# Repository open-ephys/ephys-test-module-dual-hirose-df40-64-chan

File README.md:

# Test Module for two Hirose DF40-based Headstages

This test module works with the Open Ephys
[automated ephys tester](https://github.com/open-ephys/ephys-test-board). 
It can be used to verify the functionality of:

- [Low profile 64-channel Standard](https://github.com/open-ephys/low-profile-spi-headstage-64ch)
- [Low profile 64 channel 3D](https://github.com/open-ephys/low-profile-3d-headstage-64ch)
- [ONIX Headstage-64](https://github.com/open-ephys/onix-headstage-64)
- [ONIX Headstage-64e](https://github.com/open-ephys/onix-headstage-64s)
- [ONIX Headstage-16 Stim](https://github.com/open-ephys/onix-headstage-16stim)

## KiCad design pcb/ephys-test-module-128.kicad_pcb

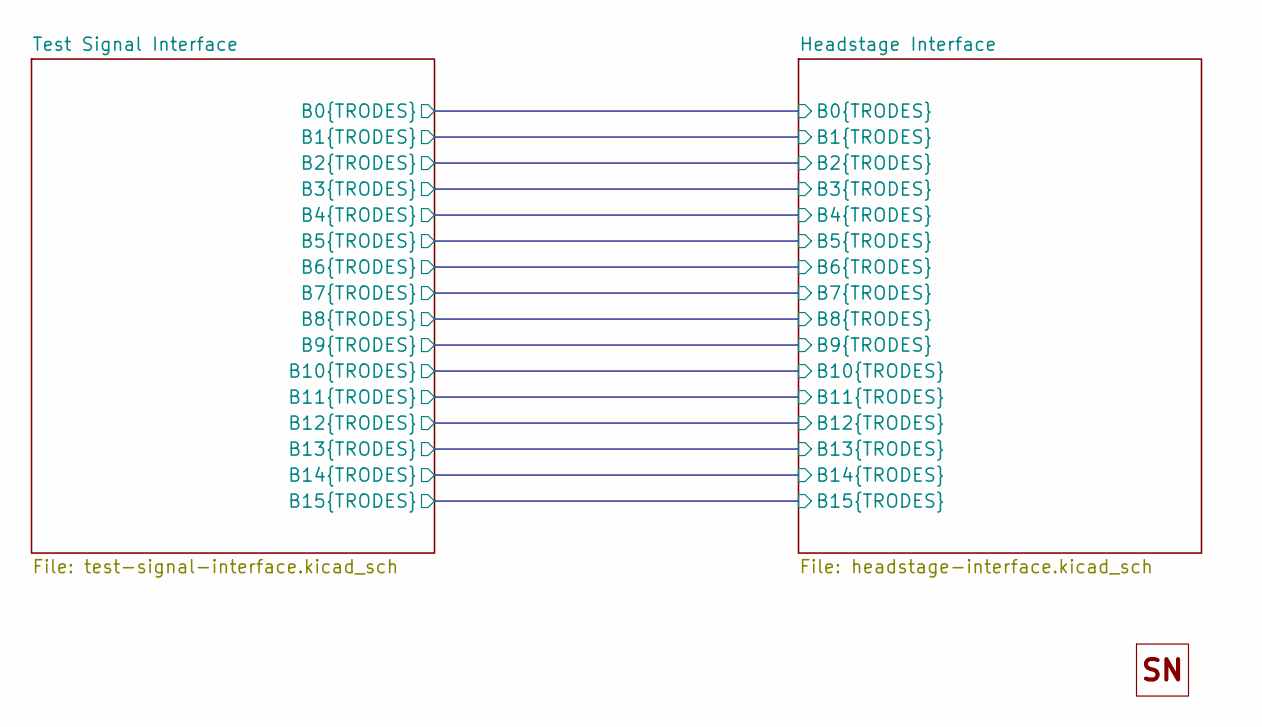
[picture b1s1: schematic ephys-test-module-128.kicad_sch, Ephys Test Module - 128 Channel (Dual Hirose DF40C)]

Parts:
H1: SN; OEPS_SN-STICKER-8x20mm; MPN n.a.

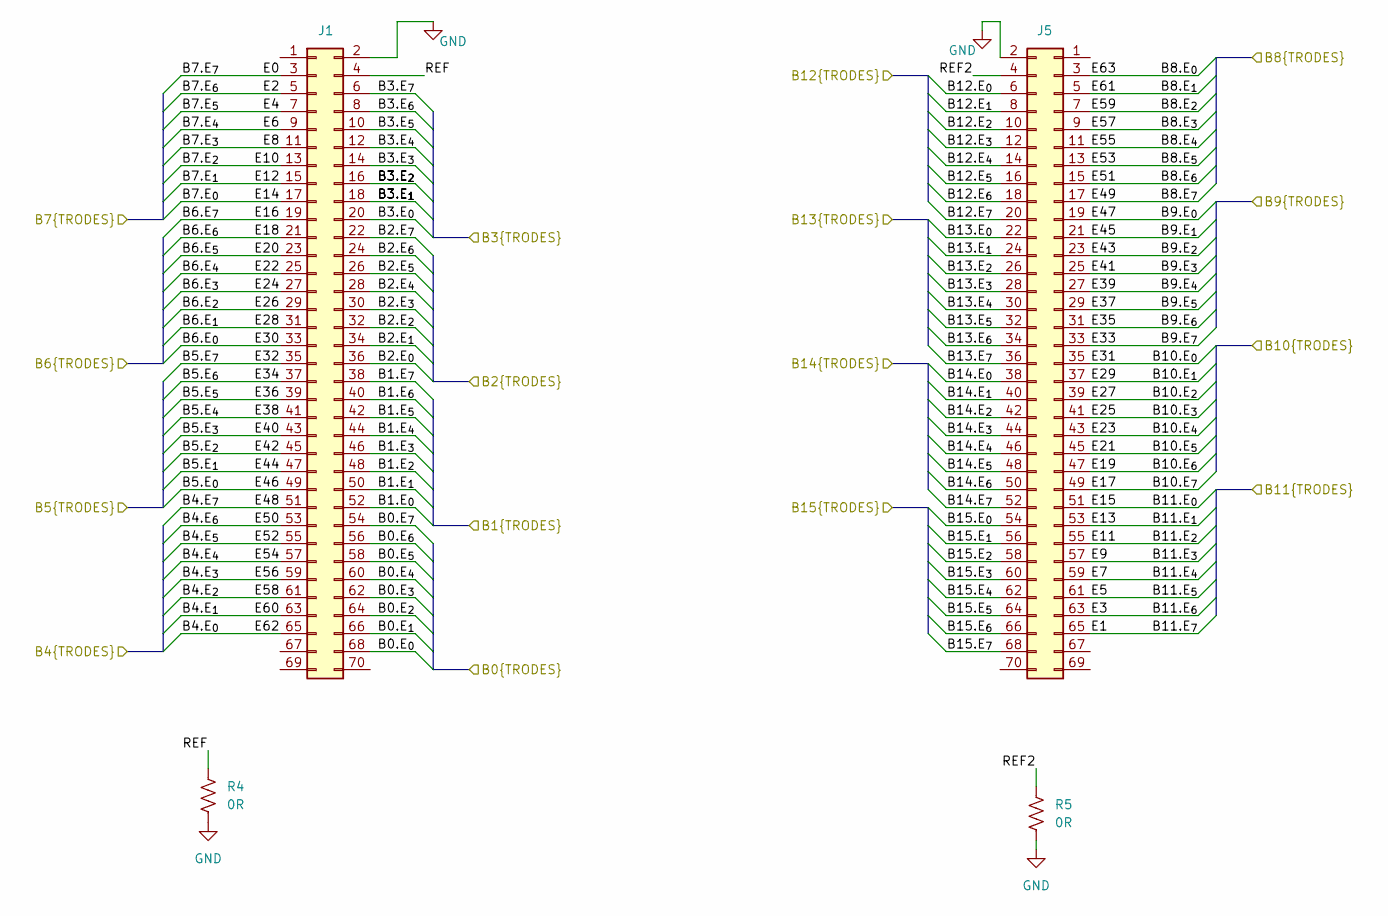
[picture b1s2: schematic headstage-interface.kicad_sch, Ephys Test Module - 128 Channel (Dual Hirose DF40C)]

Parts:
J1, J5: DF40C(2.0)-70DS-0.4V(51); HIROSE_DF40C(2.0)-70DS-0.4V(51); MPN DF40C(2.0)-70DS-0.4V(51)
R4, R5: 0R; R_0603_1608Metric; MPN RCS06030000Z0EA

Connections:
/Headstage Interface/B0.E_{0}: J1.68; also elsewhere on the board
/Headstage Interface/B0.E_{1}: J1.66; also elsewhere on the board
/Headstage Interface/B0.E_{2}: J1.64; also elsewhere on the board
/Headstage Interface/B0.E_{3}: J1.62; also elsewhere on the board
/Headstage Interface/B0.E_{4}: J1.60; also elsewhere on the board
/Headstage Interface/B0.E_{5}: J1.58; also elsewhere on the board
/Headstage Interface/B0.E_{6}: J1.56; also elsewhere on the board
/Headstage Interface/B0.E_{7}: J1.54; also elsewhere on the board
/Headstage Interface/B1.E_{0}: J1.52; also elsewhere on the board
/Headstage Interface/B1.E_{1}: J1.50; also elsewhere on the board
/Headstage Interface/B1.E_{2}: J1.48; also elsewhere on the board
/Headstage Interface/B1.E_{3}: J1.46; also elsewhere on the board
/Headstage Interface/B1.E_{4}: J1.44; also elsewhere on the board
/Headstage Interface/B1.E_{5}: J1.42; also elsewhere on the board
/Headstage Interface/B1.E_{6}: J1.40; also elsewhere on the board
/Headstage Interface/B1.E_{7}: J1.38; also elsewhere on the board
/Headstage Interface/B2.E_{0}: J1.36; also elsewhere on the board
/Headstage Interface/B2.E_{1}: J1.34; also elsewhere on the board
/Headstage Interface/B2.E_{2}: J1.32; also elsewhere on the board
/Headstage Interface/B2.E_{3}: J1.30; also elsewhere on the board
/Headstage Interface/B2.E_{4}: J1.28; also elsewhere on the board
/Headstage Interface/B2.E_{5}: J1.26; also elsewhere on the board
/Headstage Interface/B2.E_{6}: J1.24; also elsewhere on the board
/Headstage Interface/B2.E_{7}: J1.22; also elsewhere on the board
/Headstage Interface/B3.E_{0}: J1.20; also elsewhere on the board
/Headstage Interface/B3.E_{1}: J1.18; also elsewhere on the board
/Headstage Interface/B3.E_{2}: J1.16; also elsewhere on the board
/Headstage Interface/B3.E_{3}: J1.14; also elsewhere on the board
/Headstage Interface/B3.E_{4}: J1.12; also elsewhere on the board
/Headstage Interface/B3.E_{5}: J1.10; also elsewhere on the board
/Headstage Interface/B3.E_{6}: J1.8; also elsewhere on the board
/Headstage Interface/B3.E_{7}: J1.6; also elsewhere on the board
/Headstage Interface/B4.E_{0}: J1.65; also elsewhere on the board
/Headstage Interface/B4.E_{1}: J1.63; also elsewhere on the board
/Headstage Interface/B4.E_{2}: J1.61; also elsewhere on the board
/Headstage Interface/B4.E_{3}: J1.59; also elsewhere on the board
/Headstage Interface/B4.E_{4}: J1.57; also elsewhere on the board
/Headstage Interface/B4.E_{5}: J1.55; also elsewhere on the board
/Headstage Interface/B4.E_{6}: J1.53; also elsewhere on the board
/Headstage Interface/B4.E_{7}: J1.51; also elsewhere on the board
/Headstage Interface/B5.E_{0}: J1.49; also elsewhere on the board
/Headstage Interface/B5.E_{1}: J1.47; also elsewhere on the board
/Headstage Interface/B5.E_{2}: J1.45; also elsewhere on the board
/Headstage Interface/B5.E_{3}: J1.43; also elsewhere on the board
/Headstage Interface/B5.E_{4}: J1.41; also elsewhere on the board
/Headstage Interface/B5.E_{5}: J1.39; also elsewhere on the board
/Headstage Interface/B5.E_{6}: J1.37; also elsewhere on the board
/Headstage Interface/B5.E_{7}: J1.35; also elsewhere on the board
/Headstage Interface/B6.E_{0}: J1.33; also elsewhere on the board
/Headstage Interface/B6.E_{1}: J1.31; also elsewhere on the board
/Headstage Interface/B6.E_{2}: J1.29; also elsewhere on the board
/Headstage Interface/B6.E_{3}: J1.27; also elsewhere on the board
/Headstage Interface/B6.E_{4}: J1.25; also elsewhere on the board
/Headstage Interface/B6.E_{5}: J1.23; also elsewhere on the board
/Headstage Interface/B6.E_{6}: J1.21; also elsewhere on the board
/Headstage Interface/B6.E_{7}: J1.19; also elsewhere on the board
/Headstage Interface/B7.E_{0}: J1.17; also elsewhere on the board
/Headstage Interface/B7.E_{1}: J1.15; also elsewhere on the board
/Headstage Interface/B7.E_{2}: J1.13; also elsewhere on the board
/Headstage Interface/B7.E_{3}: J1.11; also elsewhere on the board
/Headstage Interface/B7.E_{4}: J1.9; also elsewhere on the board
/Headstage Interface/B7.E_{5}: J1.7; also elsewhere on the board
/Headstage Interface/B7.E_{6}: J1.5; also elsewhere on the board
/Headstage Interface/B7.E_{7}: J1.3; also elsewhere on the board
/Headstage Interface/B8.E_{0}: J5.3; also elsewhere on the board
/Headstage Interface/B8.E_{1}: J5.5; also elsewhere on the board
/Headstage Interface/B8.E_{2}: J5.7; also elsewhere on the board
/Headstage Interface/B8.E_{3}: J5.9; also elsewhere on the board
/Headstage Interface/B8.E_{4}: J5.11; also elsewhere on the board
/Headstage Interface/B8.E_{5}: J5.13; also elsewhere on the board
/Headstage Interface/B8.E_{6}: J5.15; also elsewhere on the board
/Headstage Interface/B8.E_{7}: J5.17; also elsewhere on the board
/Headstage Interface/B9.E_{0}: J5.19; also elsewhere on the board
/Headstage Interface/B9.E_{1}: J5.21; also elsewhere on the board
/Headstage Interface/B9.E_{2}: J5.23; also elsewhere on the board
/Headstage Interface/B9.E_{3}: J5.25; also elsewhere on the board
/Headstage Interface/B9.E_{4}: J5.27; also elsewhere on the board
/Headstage Interface/B9.E_{5}: J5.29; also elsewhere on the board
/Headstage Interface/B9.E_{6}: J5.31; also elsewhere on the board
/Headstage Interface/B9.E_{7}: J5.33; also elsewhere on the board
/Headstage Interface/B10.E_{0}: J5.35; also elsewhere on the board
/Headstage Interface/B10.E_{1}: J5.37; also elsewhere on the board
/Headstage Interface/B10.E_{2}: J5.39; also elsewhere on the board
/Headstage Interface/B10.E_{3}: J5.41; also elsewhere on the board
/Headstage Interface/B10.E_{4}: J5.43; also elsewhere on the board
/Headstage Interface/B10.E_{5}: J5.45; also elsewhere on the board
/Headstage Interface/B10.E_{6}: J5.47; also elsewhere on the board
/Headstage Interface/B10.E_{7}: J5.49; also elsewhere on the board
/Headstage Interface/B11.E_{0}: J5.51; also elsewhere on the board
/Headstage Interface/B11.E_{1}: J5.53; also elsewhere on the board
/Headstage Interface/B11.E_{2}: J5.55; also elsewhere on the board
/Headstage Interface/B11.E_{3}: J5.57; also elsewhere on the board
/Headstage Interface/B11.E_{4}: J5.59; also elsewhere on the board
/Headstage Interface/B11.E_{5}: J5.61; also elsewhere on the board
/Headstage Interface/B11.E_{6}: J5.63; also elsewhere on the board
/Headstage Interface/B11.E_{7}: J5.65; also elsewhere on the board
/Headstage Interface/B12.E_{0}: J5.6; also elsewhere on the board
/Headstage Interface/B12.E_{1}: J5.8; also elsewhere on the board
/Headstage Interface/B12.E_{2}: J5.10; also elsewhere on the board
/Headstage Interface/B12.E_{3}: J5.12; also elsewhere on the board
/Headstage Interface/B12.E_{4}: J5.14; also elsewhere on the board
/Headstage Interface/B12.E_{5}: J5.16; also elsewhere on the board
/Headstage Interface/B12.E_{6}: J5.18; also elsewhere on the board
/Headstage Interface/B12.E_{7}: J5.20; also elsewhere on the board
/Headstage Interface/B13.E_{0}: J5.22; also elsewhere on the board
/Headstage Interface/B13.E_{1}: J5.24; also elsewhere on the board
/Headstage Interface/B13.E_{2}: J5.26; also elsewhere on the board
/Headstage Interface/B13.E_{3}: J5.28; also elsewhere on the board
/Headstage Interface/B13.E_{4}: J5.30; also elsewhere on the board
/Headstage Interface/B13.E_{5}: J5.32; also elsewhere on the board
/Headstage Interface/B13.E_{6}: J5.34; also elsewhere on the board
/Headstage Interface/B13.E_{7}: J5.36; also elsewhere on the board
/Headstage Interface/B14.E_{0}: J5.38; also elsewhere on the board
/Headstage Interface/B14.E_{1}: J5.40; also elsewhere on the board
/Headstage Interface/B14.E_{2}: J5.42; also elsewhere on the board
/Headstage Interface/B14.E_{3}: J5.44; also elsewhere on the board
/Headstage Interface/B14.E_{4}: J5.46; also elsewhere on the board
/Headstage Interface/B14.E_{5}: J5.48; also elsewhere on the board
/Headstage Interface/B14.E_{6}: J5.50; also elsewhere on the board
/Headstage Interface/B14.E_{7}: J5.52; also elsewhere on the board
/Headstage Interface/B15.E_{0}: J5.54; also elsewhere on the board
/Headstage Interface/B15.E_{1}: J5.56; also elsewhere on the board
/Headstage Interface/B15.E_{2}: J5.58; also elsewhere on the board
/Headstage Interface/B15.E_{3}: J5.60; also elsewhere on the board
/Headstage Interface/B15.E_{4}: J5.62; also elsewhere on the board
/Headstage Interface/B15.E_{5}: J5.64; also elsewhere on the board
/Headstage Interface/B15.E_{6}: J5.66; also elsewhere on the board
/Headstage Interface/B15.E_{7}: J5.68; also elsewhere on the board
/Headstage Interface/REF: J1.4, R4.1
/Headstage Interface/REF2: J5.4, R5.1
GND: J1.2, J5.2, R4.2, R5.2; also elsewhere on the board

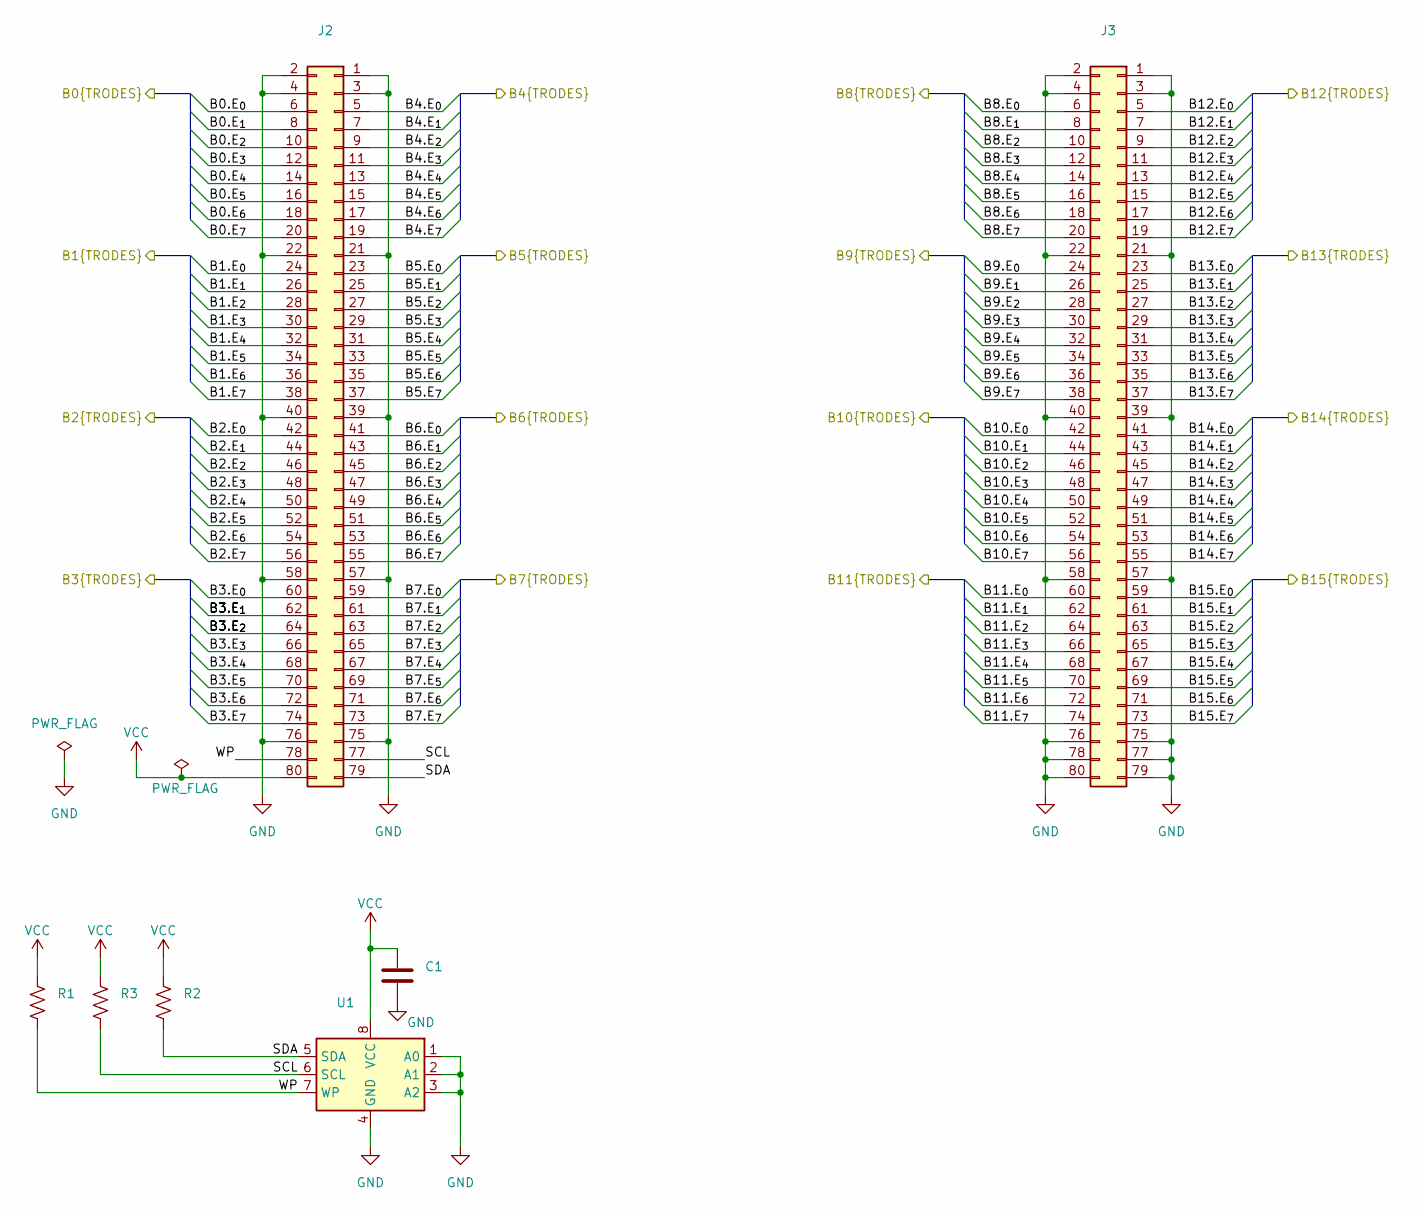
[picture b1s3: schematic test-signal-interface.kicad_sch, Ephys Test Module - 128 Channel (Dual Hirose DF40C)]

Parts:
C1: 100n; C_0402_1005Metric; MPN C1005X7R1E104K050BB
J2, J3: BSE-040-01-F-D-A-TR; SAMTEC_BSE-040-01-X-D-A; MPN BSE-040-01-F-D-A-TR
R1, R2, R3: 1k; R_0402_1005Metric; MPN CRCW04021K00FKED
U1: AT24C64D-SSHM-T; SOIC-8_3.9x4.9mm_P1.27mm; MPN AT24C64D-SSHM-T

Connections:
/Headstage Interface/B0.E_{0}: J2.6; also elsewhere on the board
/Headstage Interface/B0.E_{1}: J2.8; also elsewhere on the board
/Headstage Interface/B0.E_{2}: J2.10; also elsewhere on the board
/Headstage Interface/B0.E_{3}: J2.12; also elsewhere on the board
/Headstage Interface/B0.E_{4}: J2.14; also elsewhere on the board
/Headstage Interface/B0.E_{5}: J2.16; also elsewhere on the board
/Headstage Interface/B0.E_{6}: J2.18; also elsewhere on the board
/Headstage Interface/B0.E_{7}: J2.20; also elsewhere on the board
/Headstage Interface/B1.E_{0}: J2.24; also elsewhere on the board
/Headstage Interface/B1.E_{1}: J2.26; also elsewhere on the board
/Headstage Interface/B1.E_{2}: J2.28; also elsewhere on the board
/Headstage Interface/B1.E_{3}: J2.30; also elsewhere on the board
/Headstage Interface/B1.E_{4}: J2.32; also elsewhere on the board
/Headstage Interface/B1.E_{5}: J2.34; also elsewhere on the board
/Headstage Interface/B1.E_{6}: J2.36; also elsewhere on the board
/Headstage Interface/B1.E_{7}: J2.38; also elsewhere on the board
/Headstage Interface/B2.E_{0}: J2.42; also elsewhere on the board
/Headstage Interface/B2.E_{1}: J2.44; also elsewhere on the board
/Headstage Interface/B2.E_{2}: J2.46; also elsewhere on the board
/Headstage Interface/B2.E_{3}: J2.48; also elsewhere on the board
/Headstage Interface/B2.E_{4}: J2.50; also elsewhere on the board
/Headstage Interface/B2.E_{5}: J2.52; also elsewhere on the board
/Headstage Interface/B2.E_{6}: J2.54; also elsewhere on the board
/Headstage Interface/B2.E_{7}: J2.56; also elsewhere on the board
/Headstage Interface/B3.E_{0}: J2.60; also elsewhere on the board
/Headstage Interface/B3.E_{1}: J2.62; also elsewhere on the board
/Headstage Interface/B3.E_{2}: J2.64; also elsewhere on the board
/Headstage Interface/B3.E_{3}: J2.66; also elsewhere on the board
/Headstage Interface/B3.E_{4}: J2.68; also elsewhere on the board
/Headstage Interface/B3.E_{5}: J2.70; also elsewhere on the board
/Headstage Interface/B3.E_{6}: J2.72; also elsewhere on the board
/Headstage Interface/B3.E_{7}: J2.74; also elsewhere on the board
/Headstage Interface/B4.E_{0}: J2.5; also elsewhere on the board
/Headstage Interface/B4.E_{1}: J2.7; also elsewhere on the board
/Headstage Interface/B4.E_{2}: J2.9; also elsewhere on the board
/Headstage Interface/B4.E_{3}: J2.11; also elsewhere on the board
/Headstage Interface/B4.E_{4}: J2.13; also elsewhere on the board
/Headstage Interface/B4.E_{5}: J2.15; also elsewhere on the board
/Headstage Interface/B4.E_{6}: J2.17; also elsewhere on the board
/Headstage Interface/B4.E_{7}: J2.19; also elsewhere on the board
/Headstage Interface/B5.E_{0}: J2.23; also elsewhere on the board
/Headstage Interface/B5.E_{1}: J2.25; also elsewhere on the board
/Headstage Interface/B5.E_{2}: J2.27; also elsewhere on the board
/Headstage Interface/B5.E_{3}: J2.29; also elsewhere on the board
/Headstage Interface/B5.E_{4}: J2.31; also elsewhere on the board
/Headstage Interface/B5.E_{5}: J2.33; also elsewhere on the board
/Headstage Interface/B5.E_{6}: J2.35; also elsewhere on the board
/Headstage Interface/B5.E_{7}: J2.37; also elsewhere on the board
/Headstage Interface/B6.E_{0}: J2.41; also elsewhere on the board
/Headstage Interface/B6.E_{1}: J2.43; also elsewhere on the board
/Headstage Interface/B6.E_{2}: J2.45; also elsewhere on the board
/Headstage Interface/B6.E_{3}: J2.47; also elsewhere on the board
/Headstage Interface/B6.E_{4}: J2.49; also elsewhere on the board
/Headstage Interface/B6.E_{5}: J2.51; also elsewhere on the board
/Headstage Interface/B6.E_{6}: J2.53; also elsewhere on the board
/Headstage Interface/B6.E_{7}: J2.55; also elsewhere on the board
/Headstage Interface/B7.E_{0}: J2.59; also elsewhere on the board
/Headstage Interface/B7.E_{1}: J2.61; also elsewhere on the board
/Headstage Interface/B7.E_{2}: J2.63; also elsewhere on the board
/Headstage Interface/B7.E_{3}: J2.65; also elsewhere on the board
/Headstage Interface/B7.E_{4}: J2.67; also elsewhere on the board
/Headstage Interface/B7.E_{5}: J2.69; also elsewhere on the board
/Headstage Interface/B7.E_{6}: J2.71; also elsewhere on the board
/Headstage Interface/B7.E_{7}: J2.73; also elsewhere on the board
/Headstage Interface/B8.E_{0}: J3.6; also elsewhere on the board
/Headstage Interface/B8.E_{1}: J3.8; also elsewhere on the board
/Headstage Interface/B8.E_{2}: J3.10; also elsewhere on the board
/Headstage Interface/B8.E_{3}: J3.12; also elsewhere on the board
/Headstage Interface/B8.E_{4}: J3.14; also elsewhere on the board
/Headstage Interface/B8.E_{5}: J3.16; also elsewhere on the board
/Headstage Interface/B8.E_{6}: J3.18; also elsewhere on the board
/Headstage Interface/B8.E_{7}: J3.20; also elsewhere on the board
/Headstage Interface/B9.E_{0}: J3.24; also elsewhere on the board
/Headstage Interface/B9.E_{1}: J3.26; also elsewhere on the board
/Headstage Interface/B9.E_{2}: J3.28; also elsewhere on the board
/Headstage Interface/B9.E_{3}: J3.30; also elsewhere on the board
/Headstage Interface/B9.E_{4}: J3.32; also elsewhere on the board
/Headstage Interface/B9.E_{5}: J3.34; also elsewhere on the board
/Headstage Interface/B9.E_{6}: J3.36; also elsewhere on the board
/Headstage Interface/B9.E_{7}: J3.38; also elsewhere on the board
/Headstage Interface/B10.E_{0}: J3.42; also elsewhere on the board
/Headstage Interface/B10.E_{1}: J3.44; also elsewhere on the board
/Headstage Interface/B10.E_{2}: J3.46; also elsewhere on the board
/Headstage Interface/B10.E_{3}: J3.48; also elsewhere on the board
/Headstage Interface/B10.E_{4}: J3.50; also elsewhere on the board
/Headstage Interface/B10.E_{5}: J3.52; also elsewhere on the board
/Headstage Interface/B10.E_{6}: J3.54; also elsewhere on the board
/Headstage Interface/B10.E_{7}: J3.56; also elsewhere on the board
/Headstage Interface/B11.E_{0}: J3.60; also elsewhere on the board
/Headstage Interface/B11.E_{1}: J3.62; also elsewhere on the board
/Headstage Interface/B11.E_{2}: J3.64; also elsewhere on the board
/Headstage Interface/B11.E_{3}: J3.66; also elsewhere on the board
/Headstage Interface/B11.E_{4}: J3.68; also elsewhere on the board
/Headstage Interface/B11.E_{5}: J3.70; also elsewhere on the board
/Headstage Interface/B11.E_{6}: J3.72; also elsewhere on the board
/Headstage Interface/B11.E_{7}: J3.74; also elsewhere on the board
/Headstage Interface/B12.E_{0}: J3.5; also elsewhere on the board
/Headstage Interface/B12.E_{1}: J3.7; also elsewhere on the board
/Headstage Interface/B12.E_{2}: J3.9; also elsewhere on the board
/Headstage Interface/B12.E_{3}: J3.11; also elsewhere on the board
/Headstage Interface/B12.E_{4}: J3.13; also elsewhere on the board
/Headstage Interface/B12.E_{5}: J3.15; also elsewhere on the board
/Headstage Interface/B12.E_{6}: J3.17; also elsewhere on the board
/Headstage Interface/B12.E_{7}: J3.19; also elsewhere on the board
/Headstage Interface/B13.E_{0}: J3.23; also elsewhere on the board
/Headstage Interface/B13.E_{1}: J3.25; also elsewhere on the board
/Headstage Interface/B13.E_{2}: J3.27; also elsewhere on the board
/Headstage Interface/B13.E_{3}: J3.29; also elsewhere on the board
/Headstage Interface/B13.E_{4}: J3.31; also elsewhere on the board
/Headstage Interface/B13.E_{5}: J3.33; also elsewhere on the board
/Headstage Interface/B13.E_{6}: J3.35; also elsewhere on the board
/Headstage Interface/B13.E_{7}: J3.37; also elsewhere on the board
/Headstage Interface/B14.E_{0}: J3.41; also elsewhere on the board
/Headstage Interface/B14.E_{1}: J3.43; also elsewhere on the board
/Headstage Interface/B14.E_{2}: J3.45; also elsewhere on the board
/Headstage Interface/B14.E_{3}: J3.47; also elsewhere on the board
/Headstage Interface/B14.E_{4}: J3.49; also elsewhere on the board
/Headstage Interface/B14.E_{5}: J3.51; also elsewhere on the board
/Headstage Interface/B14.E_{6}: J3.53; also elsewhere on the board
/Headstage Interface/B14.E_{7}: J3.55; also elsewhere on the board
/Headstage Interface/B15.E_{0}: J3.59; also elsewhere on the board
/Headstage Interface/B15.E_{1}: J3.61; also elsewhere on the board
/Headstage Interface/B15.E_{2}: J3.63; also elsewhere on the board
/Headstage Interface/B15.E_{3}: J3.65; also elsewhere on the board
/Headstage Interface/B15.E_{4}: J3.67; also elsewhere on the board
/Headstage Interface/B15.E_{5}: J3.69; also elsewhere on the board
/Headstage Interface/B15.E_{6}: J3.71; also elsewhere on the board
/Headstage Interface/B15.E_{7}: J3.73; also elsewhere on the board
/Test Signal Interface/SCL: J2.77, R3.2, U1.6 (SCL)
/Test Signal Interface/SDA: J2.79, R2.2, U1.5 (SDA)
/Test Signal Interface/WP: J2.78, R1.2, U1.7 (WP)
GND: C1.2, J2.1, J2.2, J2.3, J2.4, J2.21, J2.22, J2.39, J2.40, J2.57, J2.58, J2.75, J2.76, J3.1, J3.2, J3.3, J3.4, J3.21, J3.22, J3.39, J3.40, J3.57, J3.58, J3.75, J3.76, J3.77, J3.78, J3.79, J3.80, U1.1 (A0), U1.2 (A1), U1.3 (A2), U1.4 (GND); also elsewhere on the board
VCC: C1.1, J2.80, R1.1, R2.1, R3.1, U1.8 (VCC)

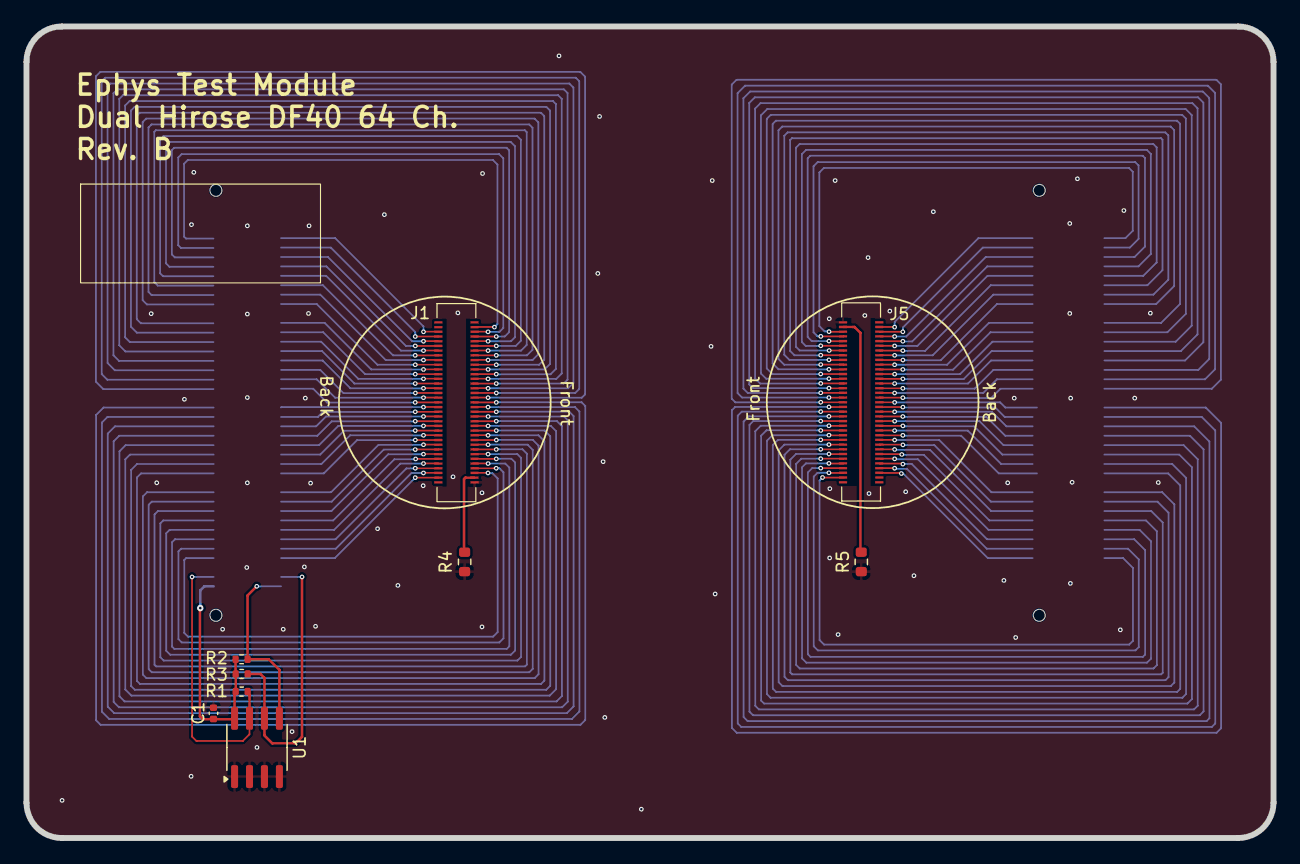
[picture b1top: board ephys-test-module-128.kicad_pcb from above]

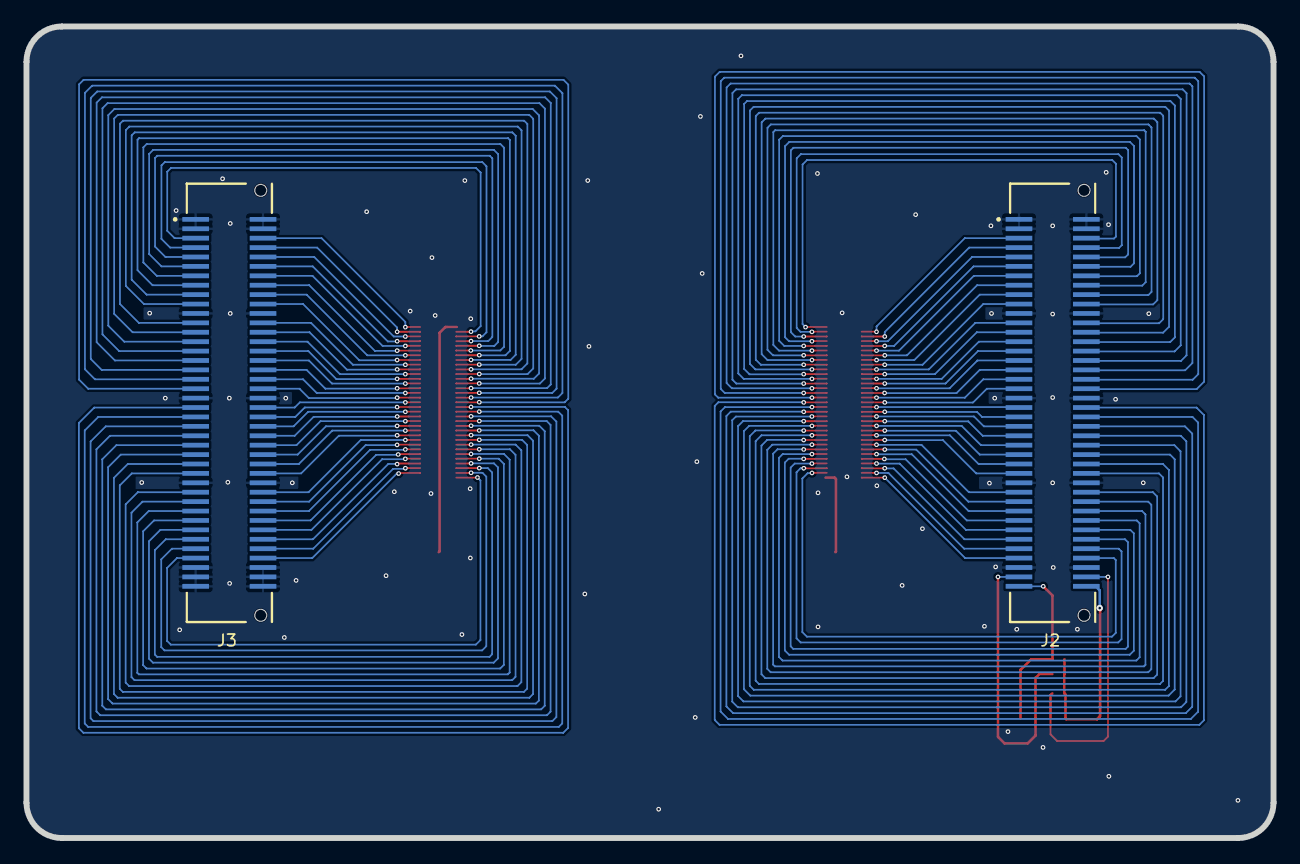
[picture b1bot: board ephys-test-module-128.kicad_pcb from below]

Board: 2 copper layers, 106.0 x 69.0 mm, 12 parts (2 on the bottom side), 135 nets.

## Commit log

2025-04-07 Initial commit.
2025-04-07 Added the PCB.
2025-04-07 Added OEPS DESC.
2025-04-07 Configure Solder Mask to Black.
2025-04-07 Added production files.
2025-04-07 Added BOM.
